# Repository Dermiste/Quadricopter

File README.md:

Quadricopter
============

## Cartes
Contient les schémas et empruntes de la carte mère (celle qui se trouve directement au dessus du Coldfire) ainsi que des 4 cartes mezzanines:
- le gyroscope                LG4200D
- l'accéléromètre             LIS331DLH
- l'accéléromètre + boussole  LMS303D
- le capteur de pression      LPS25h

## Controleur
Les sources du projet phonegap permettant de réaliser une télécommande sur smartphone/tablette

## Datasheet
Les datasheet de tous les capteurs utilisés + certains .pdf qui se sont avérés utiles

## Scilab Scripts
Tout le nécessaire pour pouvoir recevoir des données depuis la liaison série et ensuite les afficher dans un graph
À noter que l'installation d'une extension est nécessaire pour pouvoir faire fonctionner le script, disponible ici:
https://atoms.scilab.org/toolboxes/serialport

## Sources
Le code C utilisé dans le quadcopter.
Pour travailler sur un nouveau fichier basé sur l'existant, copier et renommer Sandbox.c qui contient le minimum vital (lecture capteur + filtrage) puis ajouter dans le makefile le nom du fichier dans la variable PGMs de la manière indiquée dans le commentaire juste au dessus. Noter que le makefile utilise un memory.x pour répartir certaines librairies entre la ROM et la RAM, d'ou les deux .s19 en sortie. Le "rom" est à uploader avec la sonde et ne change normalement pas (un seul upload donc, mais véto sur le "ne change pas") et le "ram" est à uploader avec dBug via un terminal.

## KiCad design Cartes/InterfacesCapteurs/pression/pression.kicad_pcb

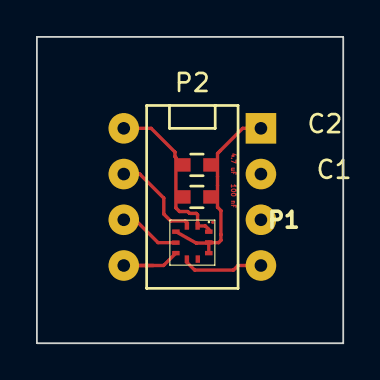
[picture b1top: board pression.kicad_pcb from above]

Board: 2 copper layers, 17.0 x 17.0 mm, 4 parts (0 on the bottom side), 6 nets.

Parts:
C1: 4.7 uF; C_0603
C2: 100 uF; C_0603
P1: DIL10; HCLGA-10L
P2: DIL8; DIP-8__300

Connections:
/CLK: P1.2, P2.2
/CS: P1.6, P2.5
/SDI: P1.4, P2.3
/SDO: P1.5, P2.4
/Vcc: C1.1, C2.1, P1.1, P1.10, P2.1
GND: C1.2, C2.2, P1.3, P1.8, P1.9, P2.8

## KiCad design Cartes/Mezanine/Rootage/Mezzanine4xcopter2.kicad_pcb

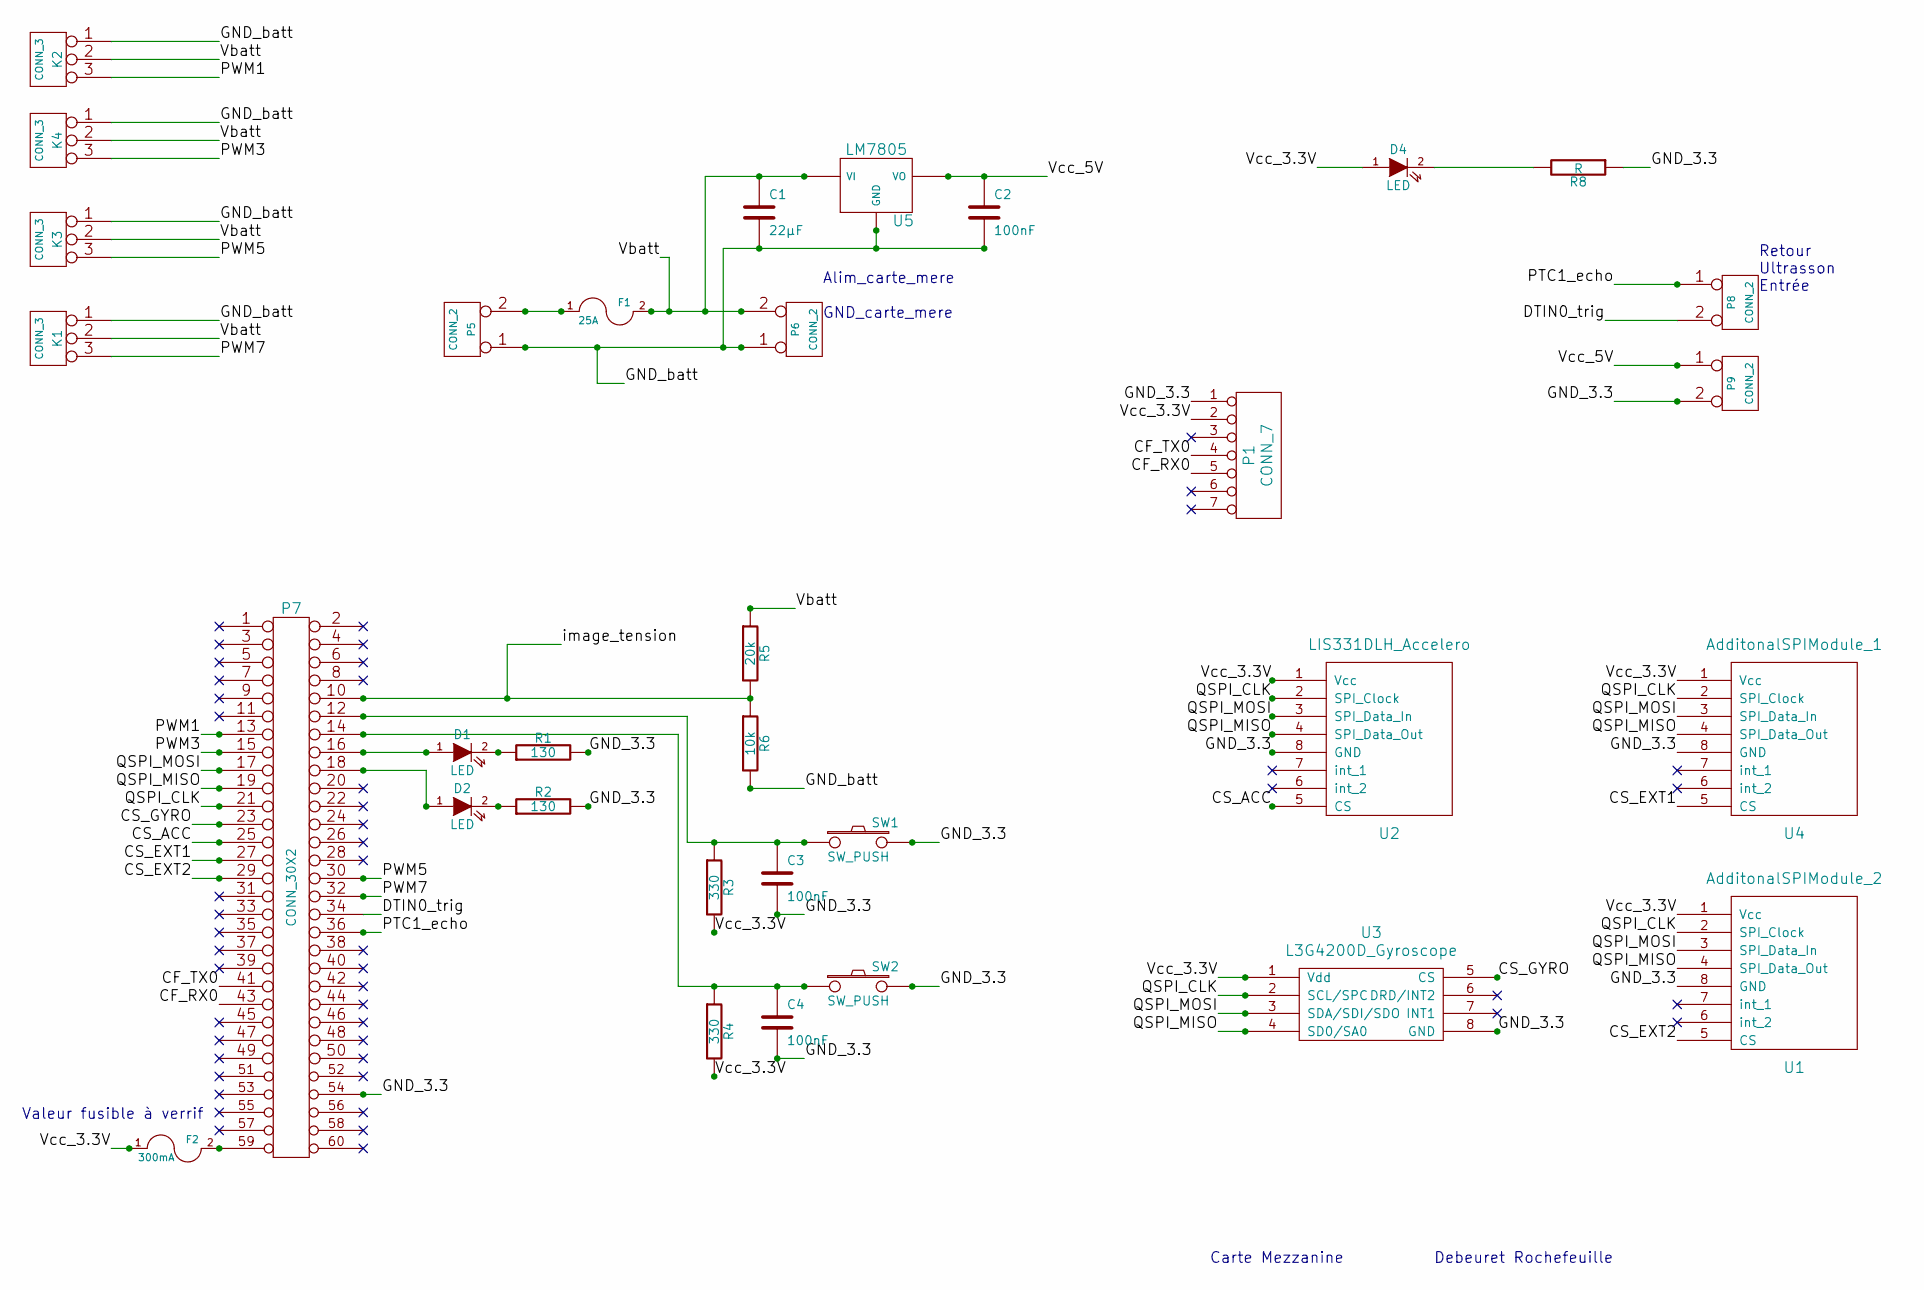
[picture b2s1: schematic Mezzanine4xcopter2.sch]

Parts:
C1: 22µF
C2, C3, C4: 100nF
D1, D2, D4: LED
F1: 25A
F2: 300mA
K1, K2, K3, K4: CONN_3
P1: CONN_7
P5, P6, P8, P9: CONN_2
P7: CONN_30X2
R1, R2: 130
R3, R4: 330
R5: 20k
R6: 10k
R8: R
SW1, SW2: SW_PUSH
U1: AdditonalSPIModule_2
U2: LIS331DLH_Accelero
U3: L3G4200D_Gyroscope
U4: AdditonalSPIModule_1
U5: LM7805

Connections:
/CF_RX0: P1.5, P7.43
/CF_TX0: P1.4, P7.41
/CS_ACC: P7.25, U2.5 (CS)
/CS_EXT1: P7.27, U4.5 (CS)
/CS_EXT2: P7.29, U1.5 (CS)
/CS_GYRO: P7.23, U3.5 (CS)
/DTIN0_trig: P7.34, P8.2 (PM)
/GND_3.3: C3.2, C4.2, P1.1, P7.54, P9.2 (PM), R1.2, R2.2, R8.1, SW1.2, SW2.2, U1.8 (GND), U2.8 (GND), U3.8 (GND), U4.8 (GND)
/GND_batt: C1.2, C2.2, K1.1, K2.1, K3.1, K4.1, P5.1, P6.1, R6.2, U5.GND
/PTC1_echo: P7.36, P8.1
/PWM1: K2.3, P7.13
/PWM3: K4.3, P7.15
/PWM5: K3.3, P7.30
/PWM7: K1.3, P7.32
/QSPI_CLK: P7.21, U1.2 (SPI_Clock), U2.2 (SPI_Clock), U3.2 (SCL/SPC), U4.2 (SPI_Clock)
/QSPI_MISO: P7.19, U1.4 (SPI_Data_Out), U2.4 (SPI_Data_Out), U3.4 (SD0/SA0), U4.4 (SPI_Data_Out)
/QSPI_MOSI: P7.17, U1.3 (SPI_Data_In), U2.3 (SPI_Data_In), U3.3 (SDA/SDI/SDO), U4.3 (SPI_Data_In)
/Vbatt: C1.1, F1.2, K1.2 (PM), K2.2 (PM), K3.2 (PM), K4.2 (PM), P6.2 (PM), R5.1, U5.VI
/Vcc_3.3V: D4.1 (A), F2.1, P1.2, R3.2, R4.2, U1.1 (Vcc), U2.1 (Vcc), U3.1 (Vdd), U4.1 (Vcc)
/Vcc_5V: C2.1, P9.1, U5.VO
/image_tension: P7.10, R5.2, R6.1
unnamed: C3.1, P7.12, R3.1, SW1.1
unnamed: C4.1, P7.14, R4.1, SW2.1
unnamed: D1.1 (A), P7.16
unnamed: D1.2 (K), R1.1
unnamed: D2.1 (A), P7.18
unnamed: D2.2 (K), R2.1
unnamed: D4.2 (K), R8.2
unnamed: F1.1, P5.2 (PM)
unnamed: F2.2, P7.59

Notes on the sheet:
Valeur fusible à verrif
Carte Mezzanine Debeuret Rochefeuille
Alim_carte_mere GND_carte_mere
Retour Ultrasson Entrée

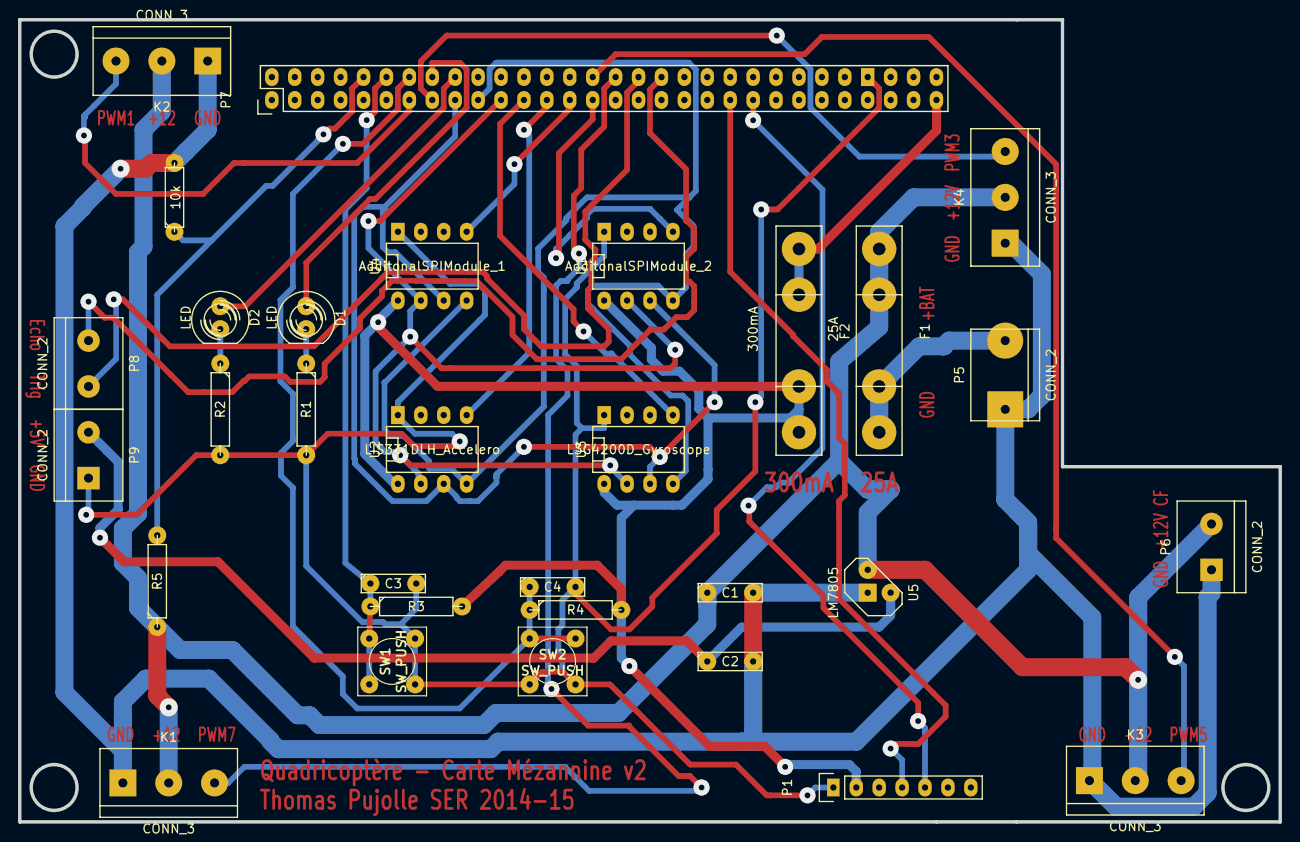
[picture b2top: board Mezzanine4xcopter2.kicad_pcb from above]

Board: 2 copper layers, 139.7 x 88.9 mm, 31 parts (0 on the bottom side), 29 nets.

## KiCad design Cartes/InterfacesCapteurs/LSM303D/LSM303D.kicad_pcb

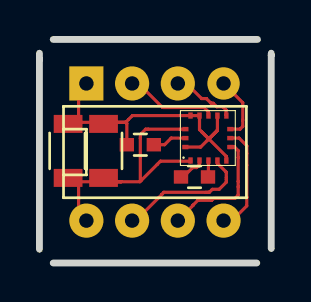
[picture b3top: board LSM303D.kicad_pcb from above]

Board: 2 copper layers, 12.9 x 12.4 mm, 6 parts (0 on the bottom side), 11 nets.

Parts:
C1: 4.7uF; C_0603
C2: 0.22uF; C_0603
C3: 10uF; C_1206
C4: 100nF; C_1206
P1: DIL8; DIP-8__300_ELL
U1: LSM303D; LGA16

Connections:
GND: C1.1, C3.1, C4.1, P1.8, U1.5, U1.10, U1.12, U1.13, U1.16
unnamed: C1.2, U1.15
unnamed: C2.1, U1.2
unnamed: C2.2, U1.3
unnamed: P1.2, U1.4
unnamed: P1.3, U1.6
unnamed: P1.4, U1.7
unnamed: P1.5, U1.8
unnamed: P1.6, U1.9
unnamed: P1.7, U1.11
VDD: C3.2, C4.2, P1.1, U1.1, U1.14

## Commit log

2014-11-27 .DS_Store banished!
2014-11-27 Add initial source files from previous years, datasheet and scilab scripts.
2014-11-30 Add readme to do's and sublime text files ignore rule
2014-11-30 renamed folder
2014-12-03 Added RéponseIndicielle and cleaned up makefile
2014-12-03 Added rules in gitignore to remove .o.s19.map
2014-12-03 removed unecessary .o.s19 and .map
2015-01-14 Extracted functions to imuUtils
2015-02-05 latest modifications
2015-02-05 added missing files
2015-02-05 new pdf
2015-02-23 latest modif
2015-02-23 cleaned up journees portes ouvertes
2015-04-08 Last modification
2015-04-08 Added phonegap controller
2015-04-08 modified readme
